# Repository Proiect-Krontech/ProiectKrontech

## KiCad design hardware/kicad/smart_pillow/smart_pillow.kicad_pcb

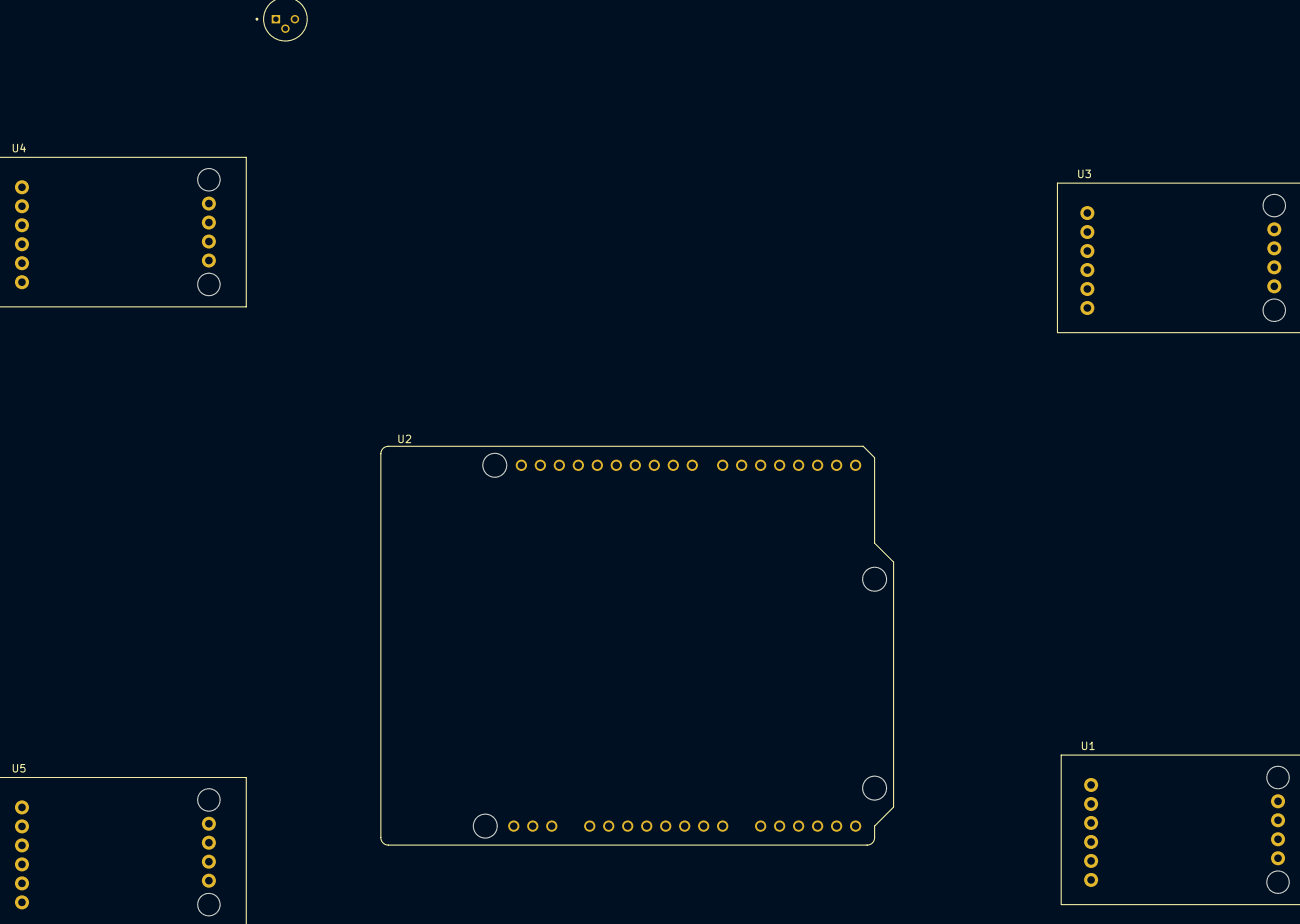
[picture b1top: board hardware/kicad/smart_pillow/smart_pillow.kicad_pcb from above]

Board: 2 copper layers, 6 parts (0 on the bottom side), 10 nets, no tracks yet.

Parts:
Q1: 2N2222A; TO127P584H533-3
U1, U3, U4, U5: HX711-Mod; HX711_module
U2: Arduino_R4_Wifi; MODULE_ABX00087

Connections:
+5V: U1.7 (VDD), U2.JA5 (+5V), U3.7 (VDD), U4.7 (VDD), U5.7 (VDD)
GND: Q1.1, U1.10 (GND), U2.JA6 (GND_JA6), U2.JA7 (GND_JA7), U2.JD15 (GND_JD15), U2.JO2 (GND_JO2), U3.10 (GND), U4.10 (GND), U5.10 (GND)
unnamed: U1.8 (CLK), U2.JD3 (D2)
unnamed: U1.9 (DAT), U2.JD4 (D3)
unnamed: U2.JD5 (D4), U4.8 (CLK)
unnamed: U2.JD6 (D5), U4.9 (DAT)
unnamed: U2.JD7 (D6), U3.8 (CLK)
unnamed: U2.JD8 (D7), U3.9 (DAT)
unnamed: U2.JD9 (D8), U5.8 (CLK)
unnamed: U2.JD10 (D9), U5.9 (DAT)

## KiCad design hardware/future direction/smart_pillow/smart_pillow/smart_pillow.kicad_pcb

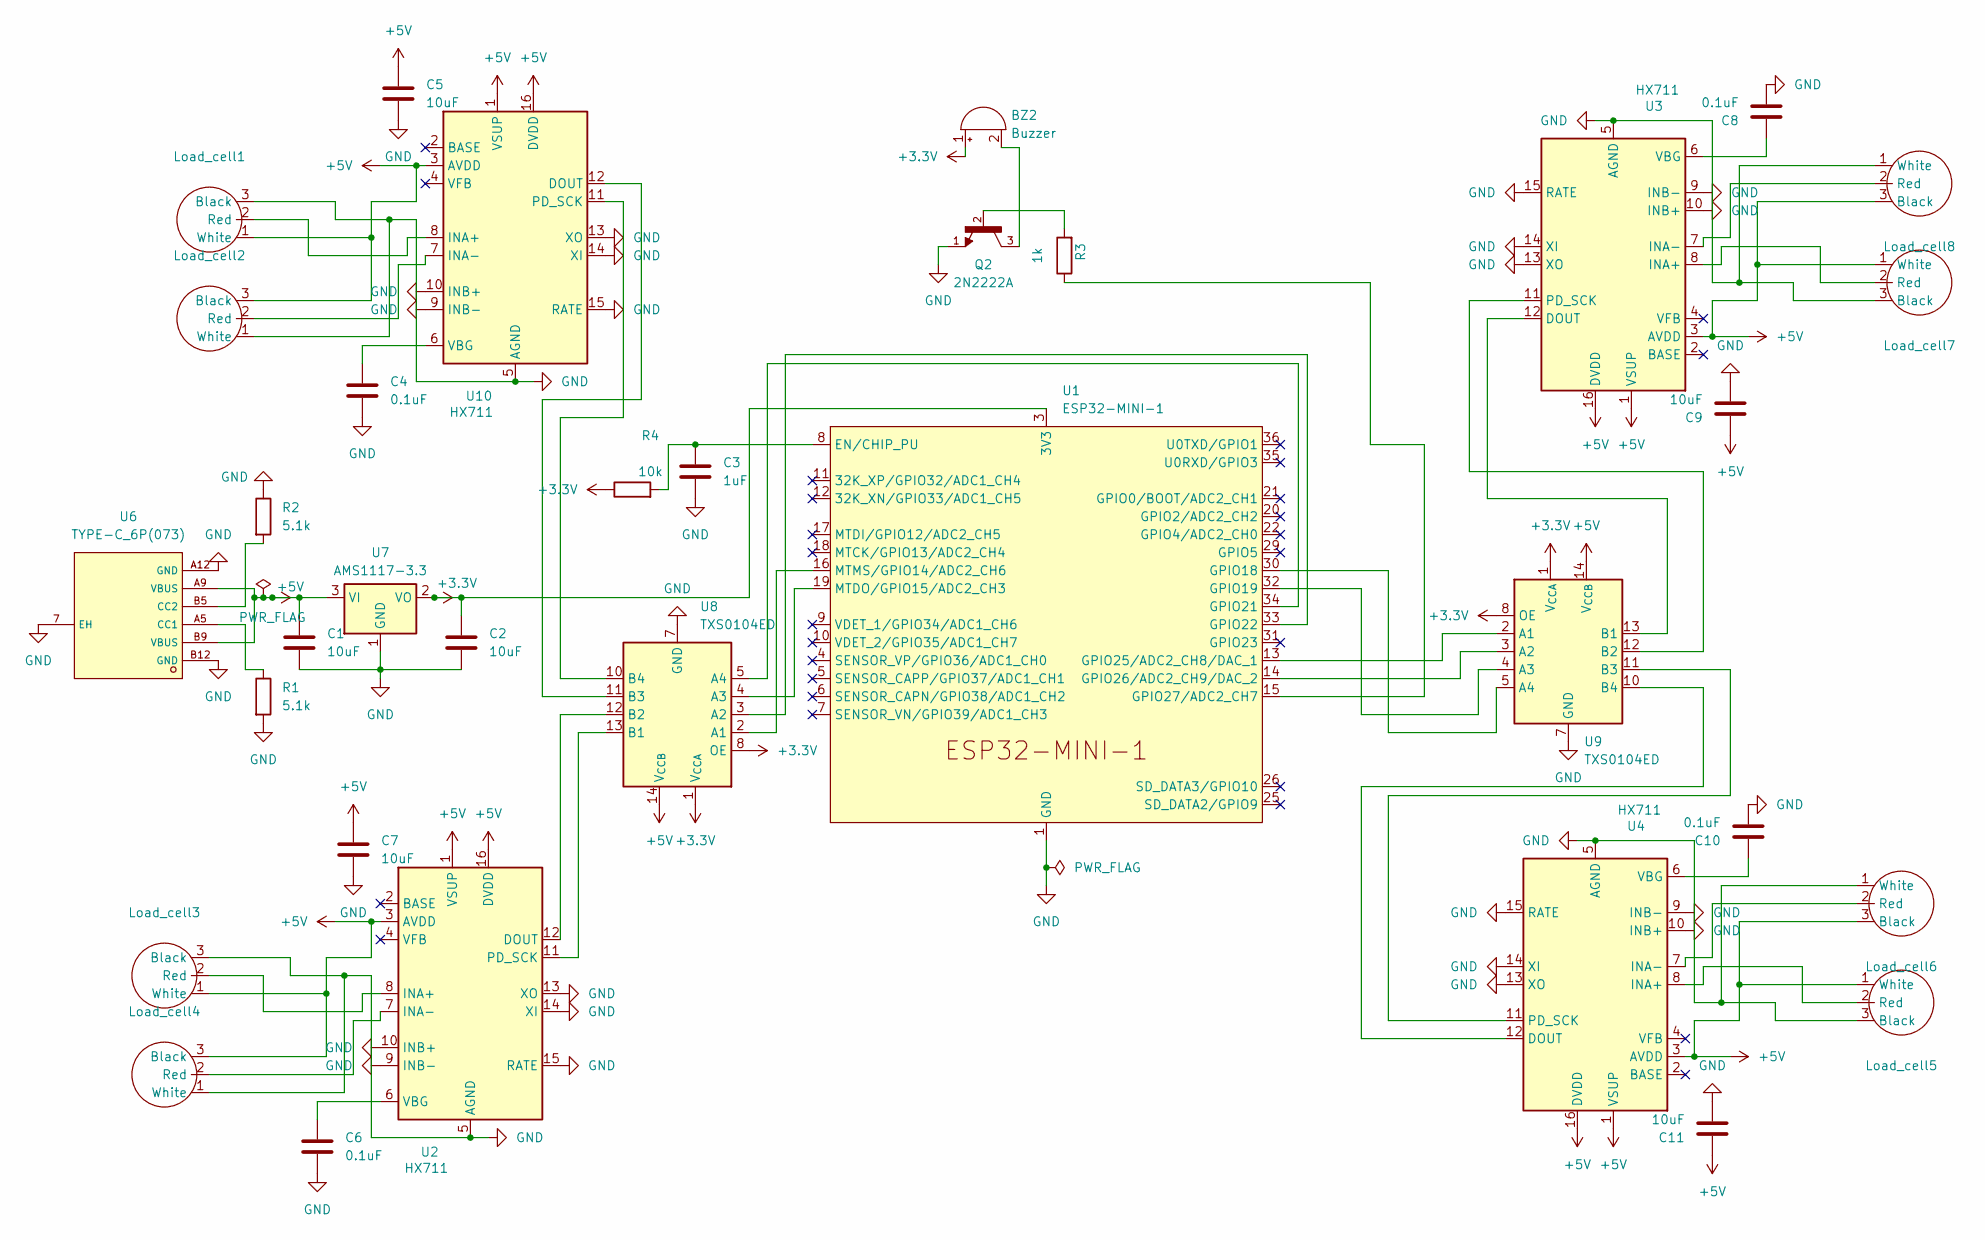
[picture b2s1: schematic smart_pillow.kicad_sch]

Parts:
BZ2: Buzzer; Buzzer_12x9.5RM7.6
C1, C2, C5, C7, C9, C11: 10uF; C_0805_2012Metric
C3: 1uF; C_0805_2012Metric
C4, C6, C8, C10: 0.1uF; C_0805_2012Metric
Load_cell1, Load_cell2, Load_cell3, Load_cell4, Load_cell5, Load_cell6, Load_cell7, Load_cell8: SolderWire-0.5sqmm_1x03_P4.8mm_D0.9mm_OD2.3mm
Q2: 2N2222A; TO127P584H533-3; PARTREV 2
R1, R2: 5.1k; R_0805_2012Metric
R3: 1k; R_0805_2012Metric
R4: 10k; R_0805_2012Metric
U1: ESP32-MINI-1
U2, U3, U4, U10: HX711; SOIC-16_3.9x9.9mm_P1.27mm
U6: TYPE-C_6P(073); TYPE-C-SMD_TYPE-C-6P-073; LCSC C668623
U7: AMS1117-3.3; SOT-223-3_TabPin2
U8, U9: TXS0104ED; SOIC-14_3.9x8.7mm_P1.27mm

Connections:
+3.3V: BZ2.1 (+), C2.1, R4.1, U1.3 (3V3), U7.2 (VO), U8.1 (V_{CCA}), U8.8 (OE), U9.1 (V_{CCA}), U9.8 (OE)
+5V: C1.1, C5.1, C7.1, C9.1, C11.1, Load_cell1.1 (White), Load_cell2.3 (Black), Load_cell3.1 (White), Load_cell4.3 (Black), Load_cell5.1 (White), Load_cell6.3 (Black), Load_cell7.1 (White), Load_cell8.3 (Black), U2.1 (VSUP), U2.3 (AVDD), U2.16 (DVDD), U3.1 (VSUP), U3.3 (AVDD), U3.16 (DVDD), U4.1 (VSUP), U4.3 (AVDD), U4.16 (DVDD), U6.A9 (VBUS), U6.B9 (VBUS), U7.3 (VI), U8.14 (V_{CCB}), U9.14 (V_{CCB}), U10.1 (VSUP), U10.3 (AVDD), U10.16 (DVDD)
GND: C1.2, C2.2, C3.2, C4.2, C5.2, C6.2, C7.2, C8.2, C9.2, C10.2, C11.2, Load_cell1.3 (Black), Load_cell2.1 (White), Load_cell3.3 (Black), Load_cell4.1 (White), Load_cell5.3 (Black), Load_cell6.1 (White), Load_cell7.3 (Black), Load_cell8.1 (White), Q2.1, R1.2, R2.1, U1.1 (GND), U1.2 (GND), U1.27 (GND), U1.38 (GND), U1.39 (GND), U1.40 (GND), U1.41 (GND), U1.42 (GND), U1.43 (GND), U1.44 (GND), U1.45 (GND), U1.46 (GND), U1.47 (GND), U1.48 (GND), U1.49 (GND), U1.50 (GND), U1.51 (GND), U1.52 (GND), U1.53 (GND), U1.54 (GND), U1.55 (GND), U2.5 (AGND), U2.9 (INB-), U2.10 (INB+), U2.13 (XO), U2.14 (XI), U2.15 (RATE), U3.5 (AGND), U3.9 (INB-), U3.10 (INB+), U3.13 (XO), U3.14 (XI), U3.15 (RATE), U4.5 (AGND), U4.9 (INB-), U4.10 (INB+), U4.13 (XO), U4.14 (XI), U4.15 (RATE), U6.7 (EH), U6.A12 (GND), U6.B12 (GND), U7.1 (GND), U8.7 (GND), U9.7 (GND), U10.5 (AGND), U10.9 (INB-), U10.10 (INB+), U10.13 (XO), U10.14 (XI), U10.15 (RATE)
unnamed: BZ2.2 (-), Q2.3
unnamed: Load_cell1.2 (Red), U10.8 (INA+)
unnamed: Load_cell2.2 (Red), U10.7 (INA-)
unnamed: Load_cell3.2 (Red), U2.8 (INA+)
unnamed: Load_cell4.2 (Red), U2.7 (INA-)
unnamed: Load_cell5.2 (Red), U4.8 (INA+)
unnamed: Load_cell6.2 (Red), U4.7 (INA-)
unnamed: Load_cell7.2 (Red), U3.8 (INA+)
unnamed: Load_cell8.2 (Red), U3.7 (INA-)
unnamed: Q2.2, R3.2
unnamed: C3.1, R4.2, U1.8 (EN/CHIP_PU)
unnamed: U1.30 (GPIO18), U9.5 (A4)
unnamed: U1.32 (GPIO19), U9.4 (A3)
unnamed: U1.34 (GPIO21), U8.5 (A4)
unnamed: U1.33 (GPIO22), U8.3 (A2)
unnamed: U1.13 (GPIO25/ADC2_CH8/DAC_1), U9.2 (A1)
unnamed: U1.14 (GPIO26/ADC2_CH9/DAC_2), U9.3 (A2)
unnamed: R3.1, U1.15 (GPIO27/ADC2_CH7)
unnamed: U1.19 (MTDO/GPIO15/ADC2_CH3), U8.4 (A3)
unnamed: U1.16 (MTMS/GPIO14/ADC2_CH6), U8.2 (A1)
unnamed: U2.12 (DOUT), U8.12 (B2)
unnamed: U2.11 (PD_SCK), U8.13 (B1)
unnamed: C6.1, U2.6 (VBG)
unnamed: U3.12 (DOUT), U9.13 (B1)
unnamed: U3.11 (PD_SCK), U9.12 (B2)
unnamed: C8.1, U3.6 (VBG)
unnamed: U4.12 (DOUT), U9.10 (B4)
unnamed: U4.11 (PD_SCK), U9.11 (B3)
unnamed: C10.1, U4.6 (VBG)
unnamed: R1.1, U6.A5 (CC1)
unnamed: R2.2, U6.B5 (CC2)
unnamed: U8.11 (B3), U10.12 (DOUT)
unnamed: U8.10 (B4), U10.11 (PD_SCK)
unnamed: C4.1, U10.6 (VBG)

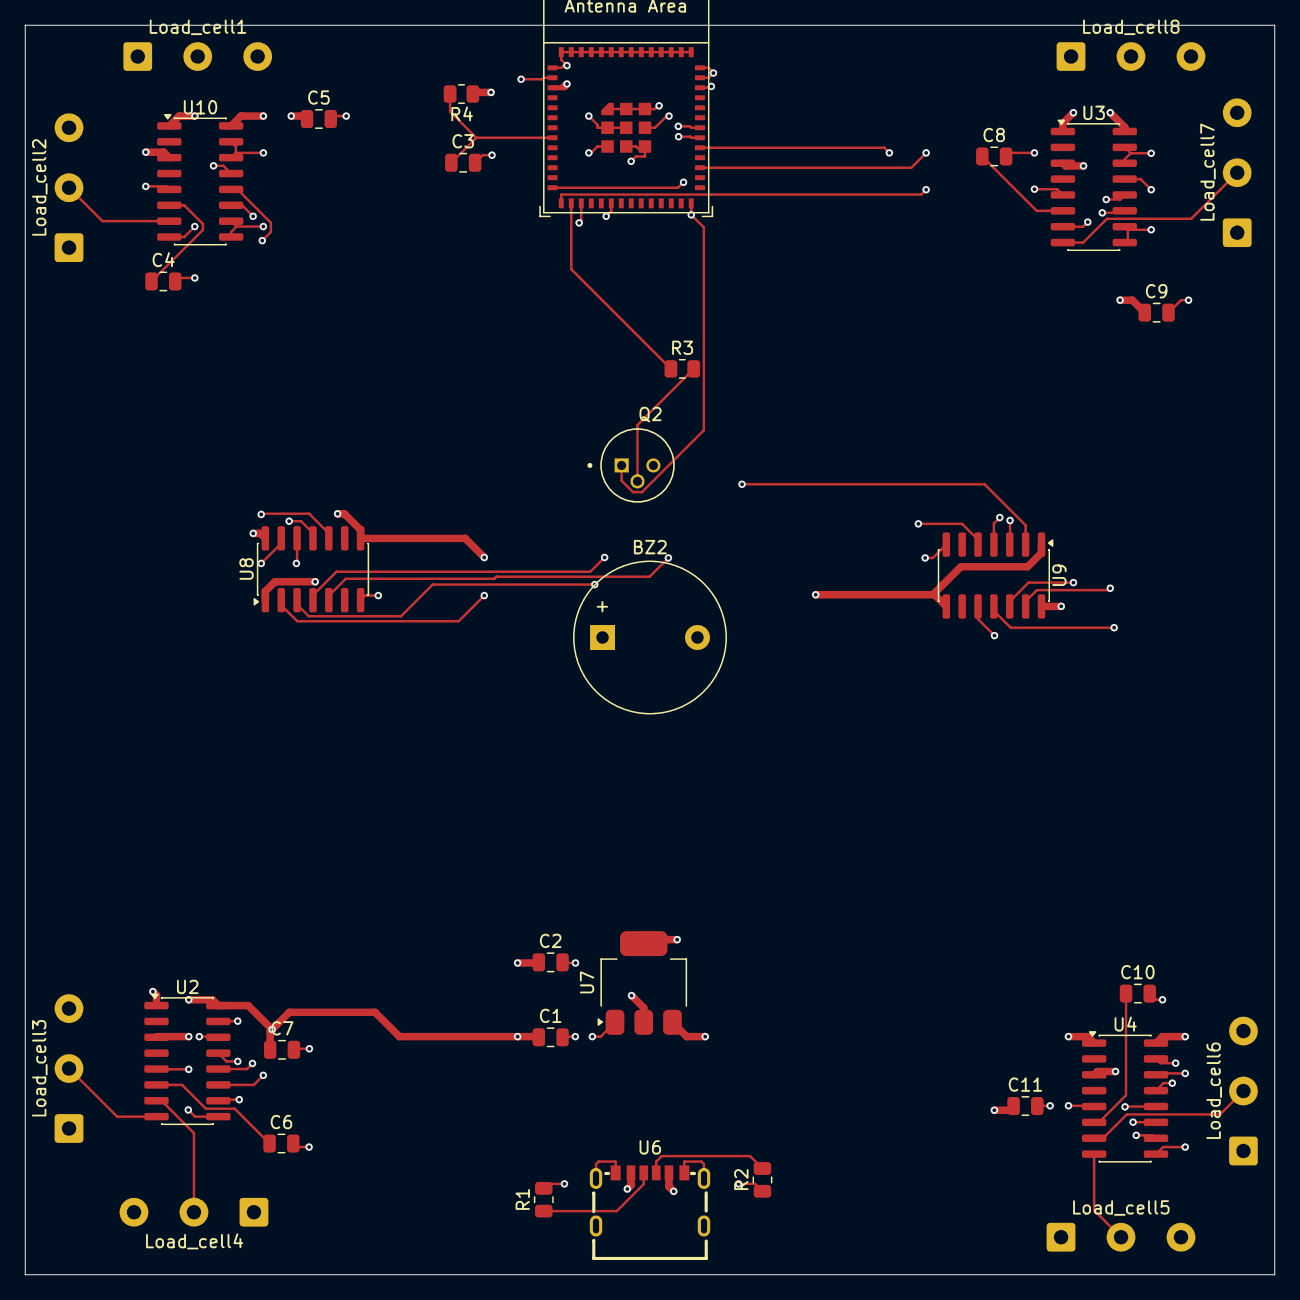
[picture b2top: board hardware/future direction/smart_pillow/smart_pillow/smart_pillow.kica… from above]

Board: 4 copper layers, 100.0 x 100.0 mm, 34 parts (0 on the bottom side), 37 nets.

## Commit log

2026-04-22 Initial commit - adaugare README
2026-04-22 Creare Foldere
2026-04-23 feat: reset project structure to official version
2026-04-23 feat: add missing project directories (backend, frontend, docs)
2026-04-26 chore(firmware-esp): create folder and add initial files
2026-04-26 chore(firmware-arduino): add module structure and placeholder files
2026-04-26 chore: remove old firmware folder
2026-04-30 refactor: remove accelerometer module and clean up related code
2026-05-04 feat: add Angular frontend project
2026-05-04 feat: add cum-functioneaza component
2026-05-04 feat: Add Navbar component
2026-05-04 feat: add features-section component
2026-05-04 Add order-form component
2026-05-04 feat: add footer component
2026-05-04 feat: add hero component
2026-05-04 feat: Add size-selector component
2026-05-04 feat: add models folder
2026-05-04 feat: Size selector component
2026-05-04 feat: Add landing-component
2026-05-04 feat: Add Store component
2026-05-04 feat: initial-setup
2026-05-04 feat: add logger
2026-05-04 feat: add config
2026-05-04 refactor: remove BuzzerPatterns.hpp
2026-05-04 feat: add AlertManager.cpp
2026-05-04 feat: add posture analyzer module
2026-05-04 feat: add AlertManager.hpp
2026-05-04 chore(posture-data): remove unnecessary comments from header
2026-05-04 chore: update platformio config for firmware-arduino
2026-05-04 feat(hx711): add HX711 driver implementation
2026-05-04 feat(sensor-manager): integrate loadcell support
2026-05-04 feat(loadcell): add iloadcell interface
2026-05-04 Revert "Merge pull request #12 from Proiect-Krontech/feature/sensor"
    This reverts commit 64bc68e4fed0c18819c82069a388de74d6149f52, reversing
    changes made to 4fe123f43013a077d18f17973678b14c3b4f3ad3.
2026-05-04 feat:add main.cpp
2026-05-05 Revert "feat: add models folder"
2026-05-06 Revert "feat: add hero component"
2026-05-06 Revert "Feature/size selector"
2026-05-06 wip: fix
2026-05-06 fix: project structure
2026-05-07 refactor: remove firmware-esp module
2026-05-07 chore: remove deprecated firmware-esp module
2026-05-07 refactor:remove redundant calibration delay and align main.cpp
2026-05-07 feat(network): add HttpClient and WifiManager
2026-05-08 feat: add storage manager integration
2026-05-09 refactor: update config setup
2026-05-09 chore: add shared secrets template
2026-05-10 chore: add hardware and docs directory structure
2026-05-10 feat(hardware): add smart_pillow KiCad project and component libraries
2026-05-10 chore: add KiCad rules to gitignore
2026-05-10 docs(hardware): add circuit schematic PDF
2026-05-10 refactor: remove unused SerialBridge module
2026-05-10 docs: replace README
2026-05-11 chore(platformio): adjust monitor speed
2026-05-13 feat: project setup - Angular frontend, Express backend, MongoDB
2026-05-13 refactor: simplify SensorManager logging
2026-05-13 fix: send device status when calibration is missing
2026-05-13 refactor: improve HTTP client connection handling
2026-05-13 fix: improve WiFi reconnection and DHCP handling
2026-05-13 chore: update wifi, server and calibration settings
2026-05-13 chore: cleanup posture logging and improve debug output
2026-05-13 chore: remove Secrets.hpp
2026-05-15 test: add QA test suite (Cypress E2E + firmware unit tests) and electrical schematics
2026-05-15 Update .gitignore to include test directory paths
2026-05-15 docs: add PCB schematics and 3D renders
2026-05-15 docs(firmware): update README - reflect new test structure
2026-05-15 docs(firmware): remove Secrets.hpp from README
2026-05-15 chore(hardware): remove .gitkeep
2026-05-15 chore(docs): restructure - move design_circuit.pdf to root docs folder
2026-05-15 chore: remove .gitkeep placeholders from backend and frontend
2026-05-16 Add Cypress and KiCad files to .gitignore
2026-05-17 docs: add project README
2026-05-17 refactor README formatting and remove emojis
2026-05-17 docs: remove credentials setup section from README
2026-05-17 docs: update README
2026-05-17 chore(docs): remove .gitkeep placeholder
2026-05-17 docs (frontend): revise README with new project title and test info
    Updated project title and modified testing instructions.
2026-05-17 docs(backend): translate README to English
